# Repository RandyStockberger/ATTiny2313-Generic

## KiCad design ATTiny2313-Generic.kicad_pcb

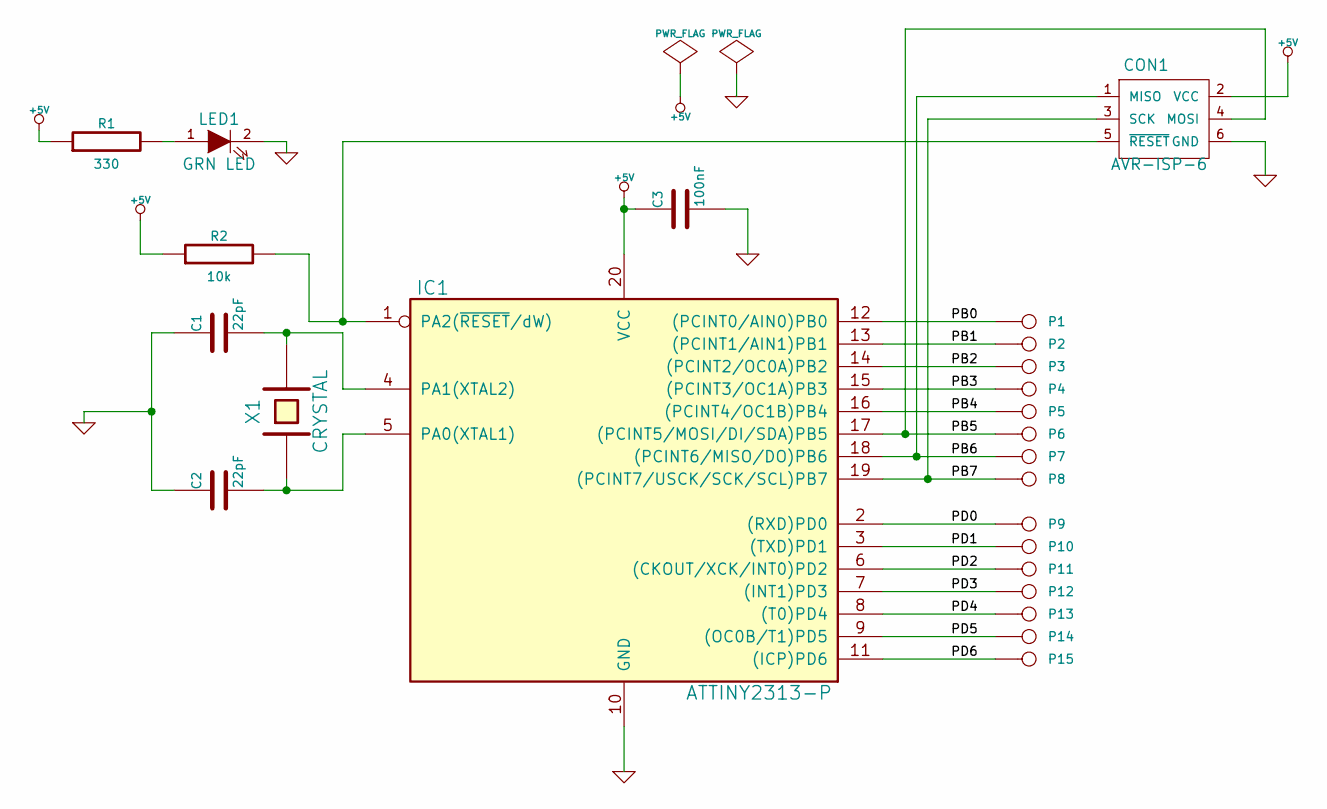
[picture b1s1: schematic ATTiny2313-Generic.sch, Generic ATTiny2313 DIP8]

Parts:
C1, C2: 22pF
C3: 100nF
CON1: AVR-ISP-6
IC1: ATTINY2313-P; DIP20
LED1: GRN LED
P1, P2, P3, P4, P5, P6, P7, P8, P9, P10, P11, P12, P13, P14, P15: CONN_1
R1: 330
R2: 10k
X1: CRYSTAL

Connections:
+5V: C3.1, CON1.2 (VCC), IC1.20 (VCC), R1.1, R2.1; also elsewhere on the board
/PB0: IC1.12 ((PCINT0/AIN0)PB0), P1.1
/PB1: IC1.13 ((PCINT1/AIN1)PB1), P2.1
/PB2: IC1.14 ((PCINT2/OC0A)PB2), P3.1
/PB3: IC1.15 ((PCINT3/OC1A)PB3), P4.1
/PB4: IC1.16 ((PCINT4/OC1B)PB4), P5.1
/PB5: CON1.4 (MOSI), IC1.17 ((PCINT5/MOSI/DI/SDA)PB5), P6.1; also elsewhere on the board
/PB6: CON1.1 (MISO), IC1.18 ((PCINT6/MISO/DO)PB6), P7.1; also elsewhere on the board
/PB7: CON1.3 (SCK), IC1.19 ((PCINT7/USCK/SCK/SCL)PB7), P8.1; also elsewhere on the board
/PD0: IC1.2 ((RXD)PD0), P9.1
/PD1: IC1.3 ((TXD)PD1), P10.1
/PD2: IC1.6 ((CKOUT/XCK/INT0)PD2), P11.1
/PD3: IC1.7 ((INT1)PD3), P12.1
/PD4: IC1.8 ((T0)PD4), P13.1
/PD5: IC1.9 ((OC0B/T1)PD5), P14.1
/PD6: IC1.11 ((ICP)PD6), P15.1
GND: C1.1, C2.1, C3.2, CON1.6 (GND), IC1.10 (GND), LED1.2 (K); also elsewhere on the board
unnamed 17: CON1.5 (~RESET), IC1.1 (PA2(~RESET~/dW)), R2.2; also elsewhere on the board
unnamed: LED1.1 (A), R1.2
unnamed: C2.2, IC1.5 (PA0(XTAL1)), X1.1
unnamed: C1.2, IC1.4 (PA1(XTAL2)), X1.2

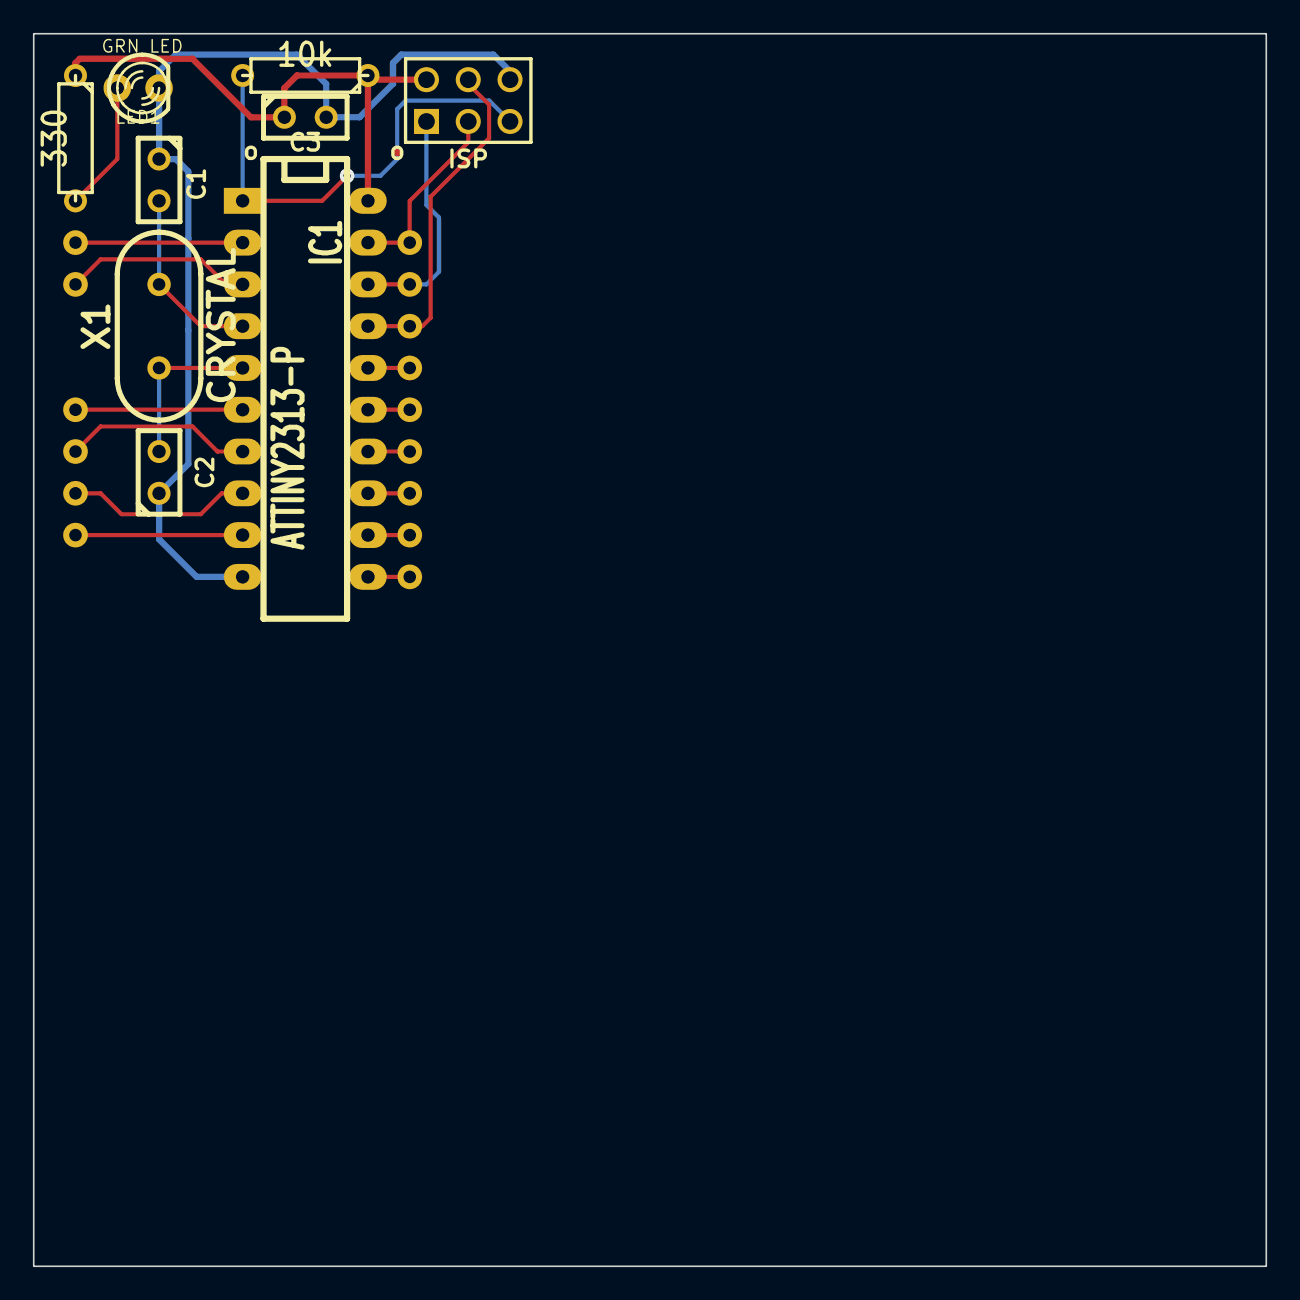
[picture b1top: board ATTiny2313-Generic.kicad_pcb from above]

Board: 2 copper layers, 74.9 x 74.9 mm, 24 parts (0 on the bottom side), 21 nets.

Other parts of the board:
ISP: AVR-ISP-6; pin_array_3x2

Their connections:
+5V: ISP.2; also elsewhere on the board
/PB5: ISP.4; also elsewhere on the board
/PB6: ISP.1; also elsewhere on the board
/PB7: ISP.3; also elsewhere on the board
GND: ISP.6; also elsewhere on the board
unnamed 17: ISP.5; also elsewhere on the board
